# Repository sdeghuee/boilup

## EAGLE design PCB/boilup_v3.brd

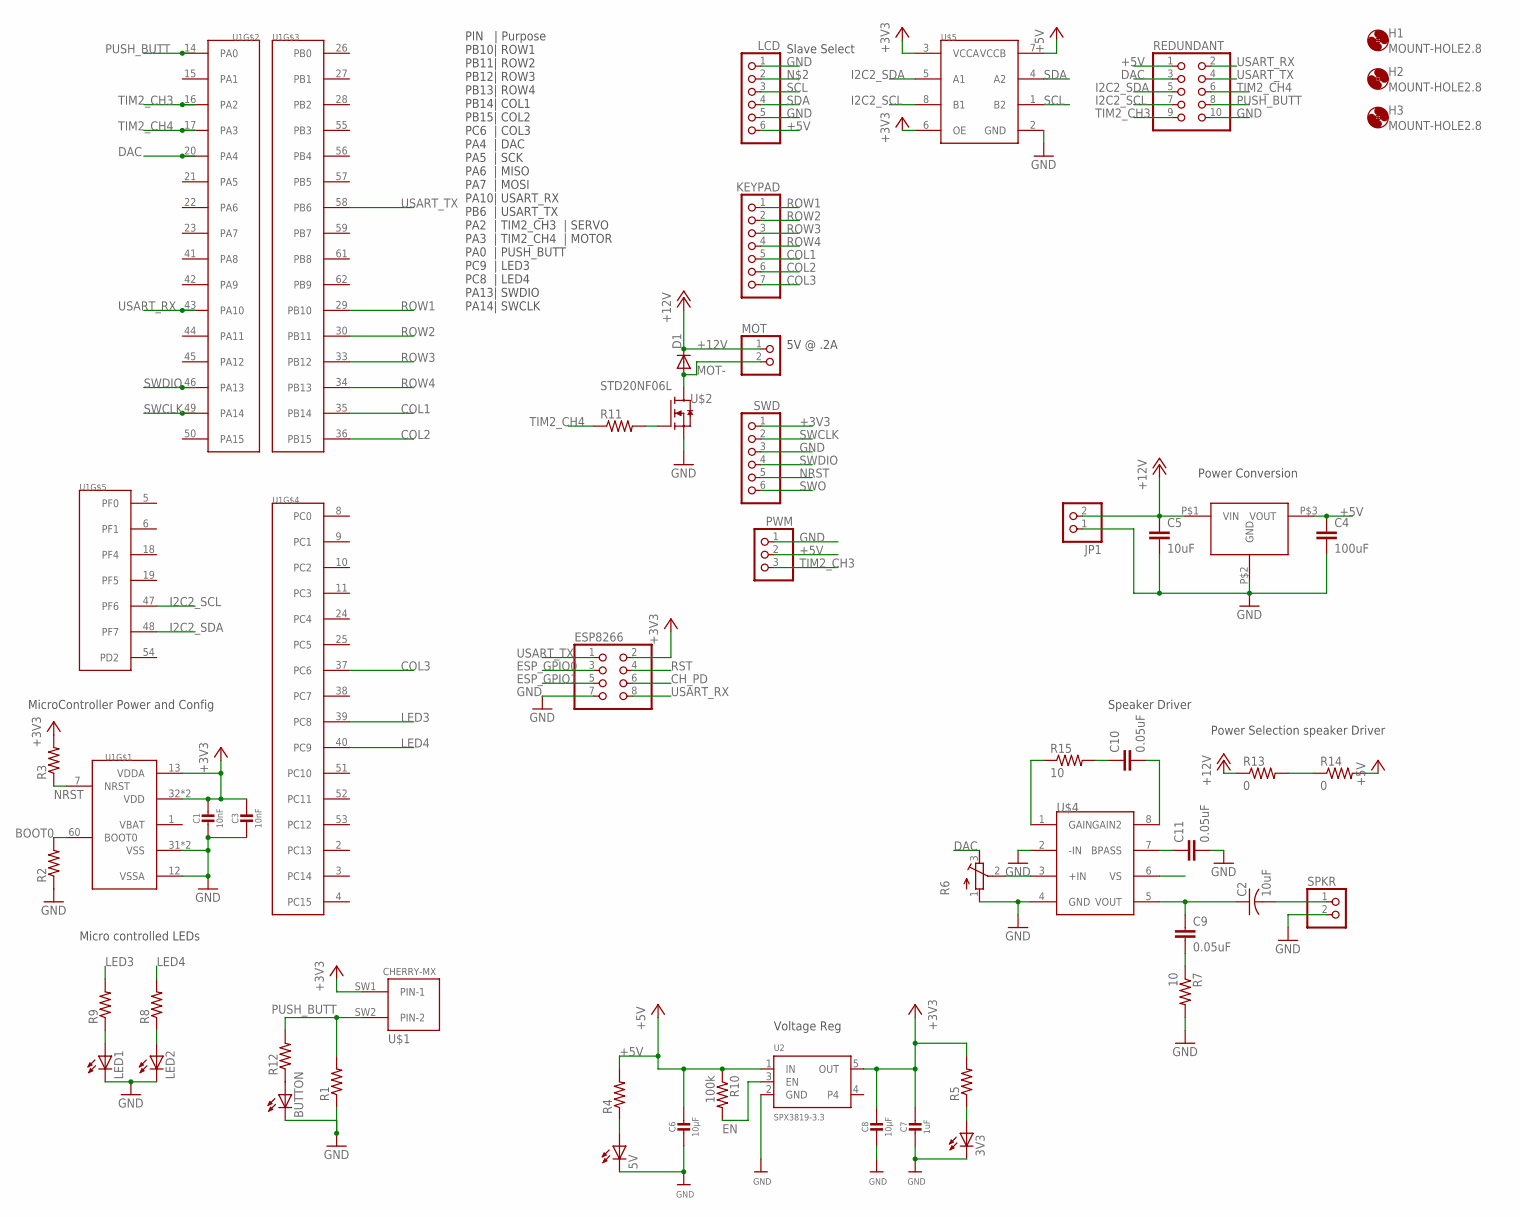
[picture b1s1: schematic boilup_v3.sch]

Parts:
3V3, 5V: LEDSML0805; SML0805
BUTTON: LEDSML0805; SML0805
C1, C3: 10nF; 0805-NO
C2: 10uF; C1210K
C4: 100uF; C1210K
C5: 10uF; C0603K
C6, C8: 10µF; 0805-NO
C7: 1uF; 0603-NO
C9, C10, C11: 0.05uF; C0603K
D1: DIODE-DO-214AC; DO-214AC
ESP8266: PINHD-2X4; 2X04
H1, H2, H3: MOUNT-HOLE2.8; 2,8
JP1: PINHD-1X2; 1X02
KEYPAD: PINHD-1X7; 1X07
LCD: PINHD-1X6; 1X06
LED1, LED2: LEDSML0805; SML0805
MOT: PINHD-1X2; 1X02
PWM: PINHD-1X3; 1X03
R1, R2, R3, R4, R5, R8, R9, R11, R12: R-US_R0603; R0603
R6: R-TRIMM3224X; RTRIM3224X
R7, R15: 10; R0603
R10: 100k; R0603
R13, R14: 0; R0603
REDUNDANT: PINHD-2X5; 2X05
SPKR: PINHD-1X2; 1X02
SWD: PINHD-1X6; 1X06
U1: STM32F0_LQFP64; QFP50P1200X1200X160-64N
U2: SPX3819-3.3; SOT23-5
U$1: CHERRY-MX
U$2: STD20NF06L; DPAK
U$3: TPSM842; TO-220
U$4: LM386; S-PDSO-G08
U$5: TXS0102; SOP-08

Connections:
+3V3: C1.1, C3.1, C7.1, C8.1, ESP8266.2, R3.2, R5.2, SWD.1, U1.13 (VDDA), U1.32 (VDD), U1.64 (VDD), U2.5 (OUT), U$1.SW1 (PIN-1), U$5.3 (VCCA), U$5.6 (OE); also elsewhere on the board
+5V: C4.1, C6.1, LCD.6, PWM.2, R4.2, R10.1, R14.2, REDUNDANT.1, U2.1 (IN), U$3.P$3 (VOUT), U$5.7 (VCCB); also elsewhere on the board
+12V: C5.1, D1.C, JP1.2, MOT.1, R13.1, U$3.P$1 (VIN); also elsewhere on the board
BOOT0: R2.2, U1.60 (BOOT0)
CH_PD: ESP8266.6
COL1: KEYPAD.5, U1.35 (PB14)
COL2: KEYPAD.6, U1.36 (PB15)
COL3: KEYPAD.7, U1.37 (PC6)
DAC: R6.3 (E), REDUNDANT.3, U1.20 (PA4)
EN: R10.2, U2.3 (EN)
ESP_GPIO0: ESP8266.3
ESP_GPIO1: ESP8266.5
GND: 3V3.C, 5V.C, BUTTON.C, C1.2, C3.2, C4.2, C5.2, C6.2, C7.2, C8.2, C11.2, ESP8266.7, JP1.1, LCD.1, LCD.5, LED1.C, LED2.C, PWM.1, R1.1, R2.1, R6.1 (A), R7.2, REDUNDANT.10, SPKR.2, SWD.3, U1.12 (VSSA), U1.31 (VSS), U1.63 (VSS), U2.2 (GND), U$2.P$2 (S), U$3.P$2 (GND), U$4.2 (-IN), U$4.4 (GND), U$5.2 (GND); also elsewhere on the board
I2C2_SCL: REDUNDANT.7, U1.47 (PF6), U$5.8 (B1); also elsewhere on the board
I2C2_SDA: REDUNDANT.5, U1.48 (PF7), U$5.5 (A1); also elsewhere on the board
LED3: R9.2, U1.39 (PC8)
LED4: R8.2, U1.40 (PC9)
MOT-: D1.A, MOT.2, U$2.P$1 (D); also elsewhere on the board
unnamed: LED2.A, R8.1
unnamed: LED1.A, R9.1
unnamed 21: R11.2, U$2.P$3 (G); also elsewhere on the board
unnamed: BUTTON.A, R12.1
unnamed: C9.2, R7.1
unnamed: 5V.A, R4.1
unnamed 25: C2.1, C9.1, U$4.5 (VOUT); also elsewhere on the board
unnamed 26: R6.2 (S), U$4.3 (+IN); also elsewhere on the board
unnamed 27: R15.1, U$4.1 (GAIN); also elsewhere on the board
unnamed 28: C10.2, U$4.8 (GAIN2); also elsewhere on the board
unnamed: C10.1, R15.2
unnamed 30: C11.1, U$4.7 (BPASS); also elsewhere on the board
unnamed: 3V3.A, R5.1
unnamed: C2.2, SPKR.1
NRST: R3.1, SWD.5, U1.7 (NRST)
OPAMPSUPPLY: R13.2, R14.1, U$4.6 (VS); also elsewhere on the board
PUSH_BUTT: R1.2, R12.2, REDUNDANT.8, U1.14 (PA0), U$1.SW2 (PIN-2)
ROW1: KEYPAD.1, U1.29 (PB10)
ROW2: KEYPAD.2, U1.30 (PB11)
ROW3: KEYPAD.3, U1.33 (PB12)
ROW4: KEYPAD.4, U1.34 (PB13)
RST: ESP8266.4
SCL: LCD.3, U$5.1 (B2); also elsewhere on the board
SDA: LCD.4, U$5.4 (A2); also elsewhere on the board
SWCLK: SWD.2, U1.49 (PA14)
SWDIO: SWD.4, U1.46 (PA13)
SWO: SWD.6
TIM2_CH3: PWM.3, REDUNDANT.9, U1.16 (PA2)
TIM2_CH4: R11.1, REDUNDANT.6, U1.17 (PA3)
USART_RX: ESP8266.8, REDUNDANT.2, U1.43 (PA10)
USART_TX: ESP8266.1, REDUNDANT.4, U1.58 (PB6)

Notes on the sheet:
PIN | Purpose PB10| ROW1 PB11| ROW2 PB12| ROW3 PB13| ROW4 PB14| COL1 PB15| COL2 PC6 | COL3 PA4 | DAC PA5 | SCK PA6 | MISO PA7 | MOSI PA10| USART_RX PB6 | USART_TX PA2 | TIM2_CH3 | SERVO PA3 | TIM2_CH4 | MOTOR PA0 | PUSH_BUTT PC9 | LED3 PC8 | LED4 PA13| SWDIO PA14| SWCLK
5V @ .2A
Voltage Reg
MicroController Power and Config
Power Conversion
Speaker Driver
Micro controlled LEDs
Power Selection speaker Driver
Slave Select

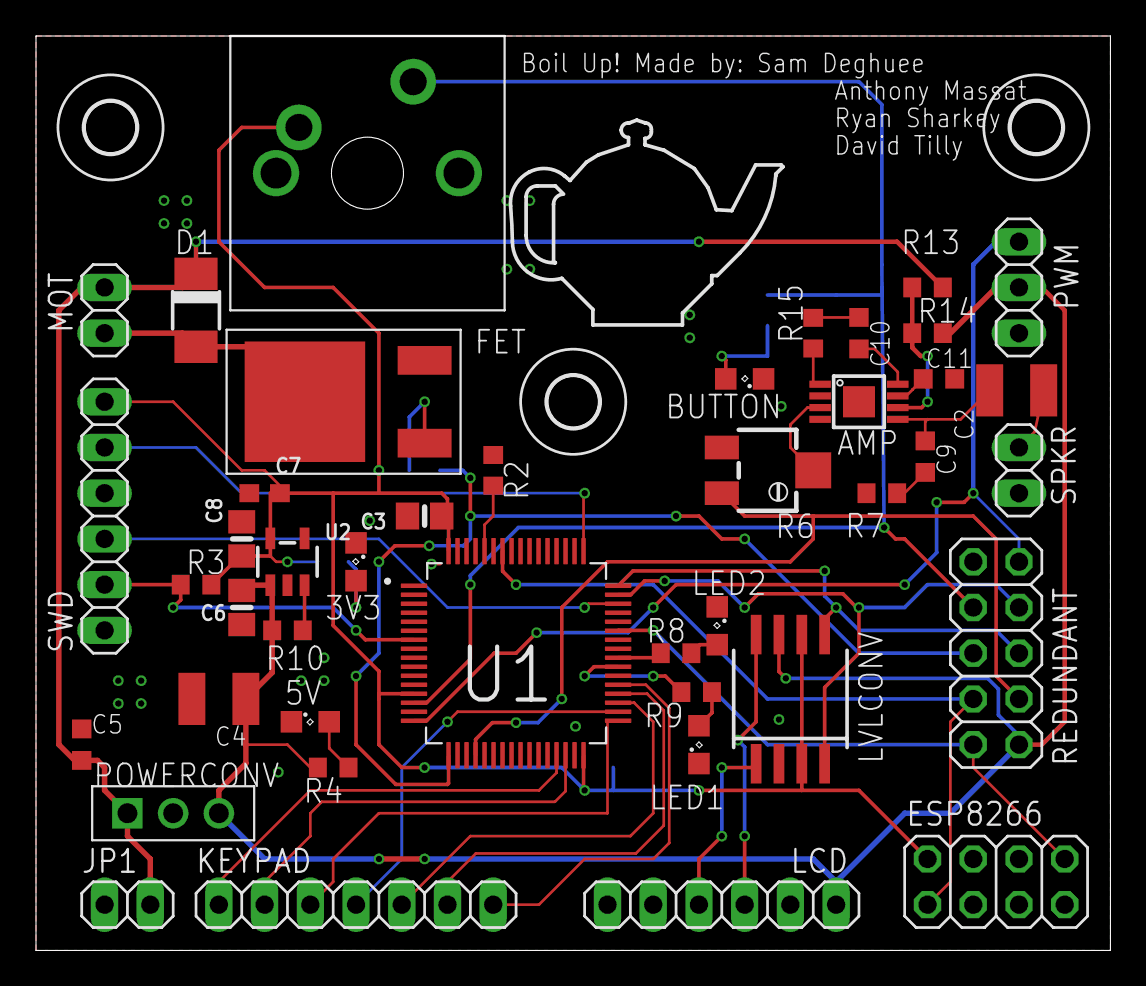
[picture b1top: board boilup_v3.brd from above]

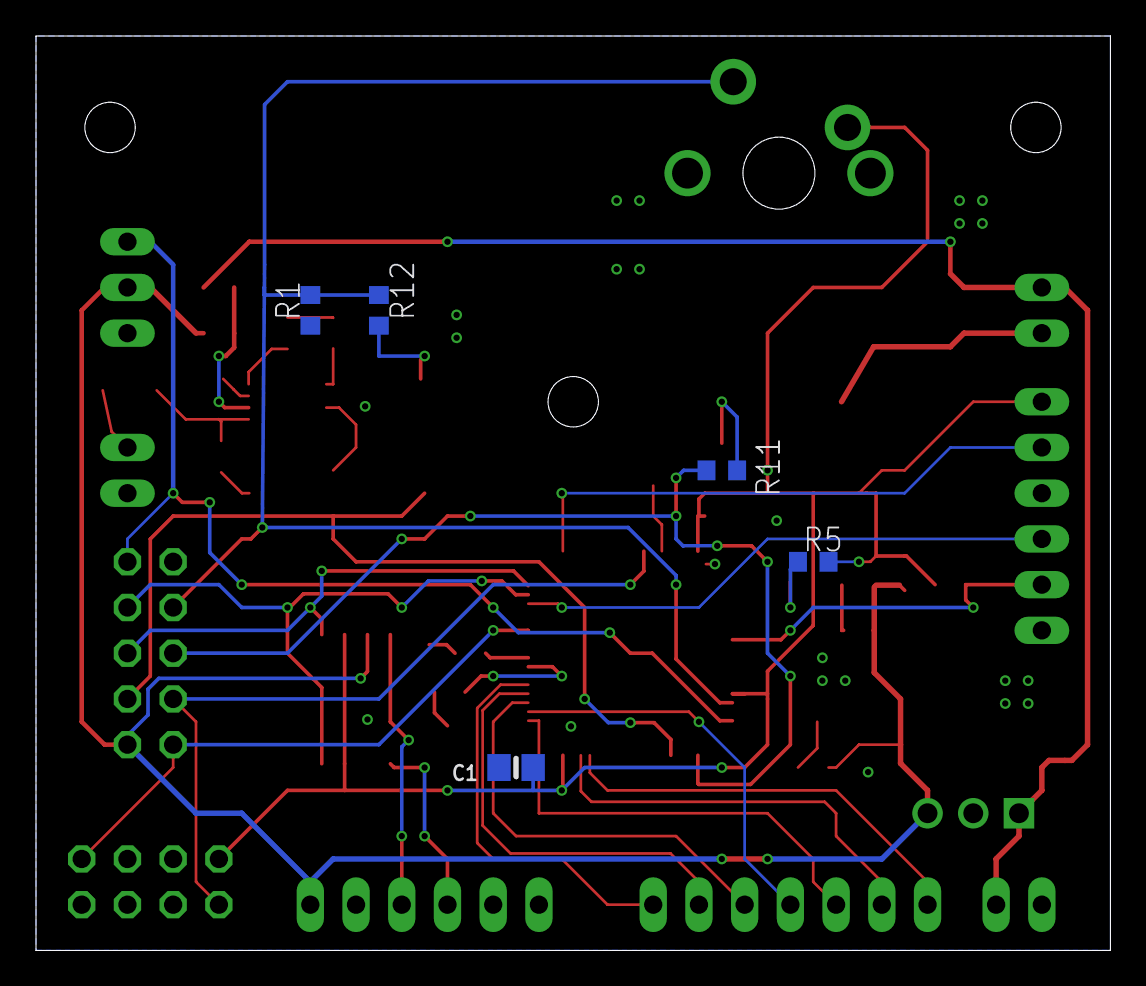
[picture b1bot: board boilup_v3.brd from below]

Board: 2 copper layers, 59.7 x 50.8 mm, 51 parts (5 on the bottom side), 44 nets.

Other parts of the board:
AMP: LM386; S-PDSO-G08
FET: STD20NF06L; DPAK
LVLCONV: TXS0102; SOP-08
POWERCONV: TPSM842; TO-220

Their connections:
+3V3: LVLCONV.3, LVLCONV.6; also elsewhere on the board
+5V: LVLCONV.7, POWERCONV.P$3; also elsewhere on the board
+12V: POWERCONV.P$1; also elsewhere on the board
GND: AMP.2, AMP.4, FET.P$2, LVLCONV.2, POWERCONV.P$2; also elsewhere on the board
I2C2_SCL: LVLCONV.4; also elsewhere on the board
I2C2_SDA: LVLCONV.5; also elsewhere on the board
MOT-: FET.P$1; also elsewhere on the board
unnamed 21: FET.P$3; also elsewhere on the board
unnamed 25: AMP.5; also elsewhere on the board
unnamed 26: AMP.3; also elsewhere on the board
unnamed 27: AMP.1; also elsewhere on the board
unnamed 28: AMP.8; also elsewhere on the board
unnamed 30: AMP.7; also elsewhere on the board
OPAMPSUPPLY: AMP.6; also elsewhere on the board
SCL: LVLCONV.1; also elsewhere on the board
SDA: LVLCONV.8; also elsewhere on the board

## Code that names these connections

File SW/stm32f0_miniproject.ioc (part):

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Mcu.Name=STM32F051R8Tx
Mcu.Package=LQFP64
Mcu.UserName=STM32F051R8Tx
PA0.GPIOParameters=GPIO_Label,GPIO_ModeDefaultEXTI
PA0.GPIO_Label=B1 [Blue PushButton]
PA0.GPIO_ModeDefaultEXTI=GPIO_MODE_EVT_RISING
PA0.Signal=GPXTI0
PA10.Mode=Asynchronous
PA10.Signal=USART1_RX
PA13.GPIOParameters=GPIO_Label
PA13.GPIO_Label=SWDIO
PA13.Signal=SYS_SWDIO
PA14.GPIOParameters=GPIO_Label
PA14.GPIO_Label=SWCLK
PA14.Signal=SYS_SWCLK
PA2.Signal=S_TIM2_CH3
PA3.Signal=S_TIM2_CH4
PA4.Signal=COMP_DAC11_group
PB10.Signal=GPIO_Input
PB11.Signal=GPIO_Input
PB12.Signal=GPIO_Input
PB13.Signal=GPIO_Input
PB14.Signal=GPIO_Output
PB15.Signal=GPIO_Output
PB6.Mode=Asynchronous
PB6.Signal=USART1_TX
PC6.Signal=GPIO_Output
PC8.GPIOParameters=GPIO_Label
PC8.GPIO_Label=LD4 [Blue Led]
PC8.Signal=GPIO_Output
PC9.GPIOParameters=GPIO_Label
PC9.GPIO_Label=LD3 [Green Led]
PC9.Signal=GPIO_Output
PF6.Mode=I2C
PF6.Signal=I2C2_SCL
PF7.Mode=I2C
PF7.Signal=I2C2_SDA
RCC.SYSCLKFreq_VALUE=48000000
RCC.SYSCLKSource=RCC_SYSCLKSOURCE_PLLCLK
board=STM32F0DISCOVERY
boardIOC=true

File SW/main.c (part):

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  /* USER CODE END WHILE */

  /* USER CODE BEGIN 3 */
//      HAL_GPIO_WritePin(COL2_PORT, COL2_PIN, 1);
//      HAL_GPIO_WritePin(COL3_PORT, COL3_PIN, 1);
//      HAL_GPIO_WritePin(COL1_PORT, COL1_PIN, 0);
//      int tmp = ROW1_PIN;
//      if (HAL_GPIO_ReadPin(ROW1_PORT, ROW1_PIN) & tmp) {
//          HAL_GPIO_WritePin(LD3_GPIO_Port, LD3_Pin, 1);
//      }
//      else {
//          HAL_GPIO_WritePin(LD3_GPIO_Port, LD3_Pin, 0);
//      }
//      HAL_GPIO_WritePin(COL1_PORT, COL1_PIN, 1);
      if (buttonPress) {
          buttonPress = 0;
          HAL_GPIO_TogglePin(LD4_GPIO_Port, LD4_Pin);
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  GPIO_InitStruct.Pull = GPIO_NOPULL;
  HAL_GPIO_Init(B1_GPIO_Port, &GPIO_InitStruct);

  /*Configure GPIO pins : PB10 PB11 PB12 PB13 */
  GPIO_InitStruct.Pin = GPIO_PIN_10|GPIO_PIN_11|GPIO_PIN_12|GPIO_PIN_13;
  GPIO_InitStruct.Mode = GPIO_MODE_INPUT;
  GPIO_InitStruct.Pull = GPIO_NOPULL;
  HAL_GPIO_Init(GPIOB, &GPIO_InitStruct);

  /*Configure GPIO pins : PB14 PB15 */
  GPIO_InitStruct.Pin = GPIO_PIN_14|GPIO_PIN_15;
  GPIO_InitStruct.Mode = GPIO_MODE_OUTPUT_PP;
  GPIO_InitStruct.Pull = GPIO_NOPULL;
  GPIO_InitStruct.Speed = GPIO_SPEED_FREQ_LOW;
  HAL_GPIO_Init(GPIOB, &GPIO_InitStruct);

  /*Configure GPIO pins : PC6 LD4_Pin LD3_Pin */
  GPIO_InitStruct.Pin = GPIO_PIN_6|LD4_Pin|LD3_Pin;
  GPIO_InitStruct.Mode = GPIO_MODE_OUTPUT_PP;
  GPIO_InitStruct.Pull = GPIO_NOPULL;
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
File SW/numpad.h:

/*
 * numpad.h
 *
 *  Created on: Apr 17, 2018
 *      Author: david
 */

#ifndef NUMPAD_H_
#define NUMPAD_H_

#define ROW1_PORT	GPIOB
#define ROW2_PORT	GPIOB
#define ROW3_PORT	GPIOB
#define ROW4_PORT	GPIOB
#define COL1_PORT	GPIOB
#define COL2_PORT	GPIOB
#define COL3_PORT	GPIOC
#define ROW1_PIN	GPIO_PIN_10
#define ROW2_PIN	GPIO_PIN_11
#define ROW3_PIN	GPIO_PIN_12
#define ROW4_PIN	GPIO_PIN_13
#define COL1_PIN	GPIO_PIN_14
#define COL2_PIN	GPIO_PIN_15
#define COL3_PIN	GPIO_PIN_6

void matrixDebounce(uint32_t column);
uint32_t matrixButtonDebounce(uint32_t index);

void matrixDebounce(uint32_t column){
    switch (column) {
        case 1:
//            GPIOC->ODR |= 0x00001000;//col3
//            GPIOD->ODR |= 0x00000004;//col2
//            GPIOB->ODR &= 0xFFFFFFF7;//col1
            HAL_GPIO_WritePin(COL2_PORT, COL2_PIN, 1);
            HAL_GPIO_WritePin(COL3_PORT, COL3_PIN, 1);
            HAL_GPIO_WritePin(COL1_PORT, COL1_PIN, 0);
            break;
        case 2:
//            GPIOB->ODR |= 0x00000008;
//            GPIOC->ODR |= 0x00001000;
//            GPIOD->ODR &= 0xFFFFFFFB;
            HAL_GPIO_WritePin(COL1_PORT, COL1_PIN, 1);
            HAL_GPIO_WritePin(COL3_PORT, COL3_PIN, 1);
            HAL_GPIO_WritePin(COL2_PORT, COL2_PIN, 0);
            break;
        case 3:
//            GPIOB->ODR |= 0x00000008;
//            GPIOD->ODR |= 0x00000004;
//            GPIOC->ODR &= 0xFFFFEFFF;
            HAL_GPIO_WritePin(COL1_PORT, COL1_PIN, 1);
            HAL_GPIO_WritePin(COL2_PORT, COL2_PIN, 1);
            HAL_GPIO_WritePin(COL3_PORT, COL3_PIN, 0);
            break;
    }
    for (uint32_t row = 0; row < 4; row++) {
//        btnCurrent[(column - 1)*4 + row] = !(GPIOB->IDR & (0x10 << (3-row)));
        switch (row) {
            case 0:
                btnCurrent[(column - 1)*4 + row] = !(HAL_GPIO_ReadPin(GPIOB, GPIO_PIN_10));
                break;
            case 1:
                btnCurrent[(column - 1)*4 + row] = !(HAL_GPIO_ReadPin(GPIOB, GPIO_PIN_11));
                break;
            case 2:
                btnCurrent[(column - 1)*4 + row] = !(HAL_GPIO_ReadPin(GPIOB, GPIO_PIN_12));
                break;
            case 3:
                btnCurrent[(column - 1)*4 + row] = !(HAL_GPIO_ReadPin(GPIOB, GPIO_PIN_13));
                break;
        }
//        uint32_t a = !(GPIOB->IDR & (0x400 << row));
//        btnCurrent[(column - 1)*4 + row] = a;
        matrixButtonDebounce((column - 1)*4 + row);
    }
}

uint32_t matrixButtonDebounce(uint32_t index) {
    btnPress[index] = !btnPrevious[index] && btnCurrent[index];
    btnPrevious[index] = btnCurrent[index];
}

#endif /* NUMPAD_H_ */

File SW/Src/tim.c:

/**
  ******************************************************************************
  * File Name          : TIM.c
  * Description        : This file provides code for the configuration
  *                      of the TIM instances.
  ******************************************************************************
  ** This notice applies to any and all portions of this file
  * that are not between comment pairs USER CODE BEGIN and
  * USER CODE END. Other portions of this file, whether 
  * inserted by the user or by software development tools
  * are owned by their respective copyright owners.
  *
  * COPYRIGHT(c) 2018 STMicroelectronics
  *
  * Redistribution and use in source and binary forms, with or without modification,
  * are permitted provided that the following conditions are met:
  *   1. Redistributions of source code must retain the above copyright notice,
  *      this list of conditions and the following disclaimer.
  *   2. Redistributions in binary form must reproduce the above copyright notice,
  *      this list of conditions and the following disclaimer in the documentation
  *      and/or other materials provided with the distribution.
  *   3. Neither the name of STMicroelectronics nor the names of its contributors
  *      may be used to endorse or promote products derived from this software
  *      without specific prior written permission.
  *
  * THIS SOFTWARE IS PROVIDED BY THE COPYRIGHT HOLDERS AND CONTRIBUTORS "AS IS"
  * AND ANY EXPRESS OR IMPLIED WARRANTIES, INCLUDING, BUT NOT LIMITED TO, THE
  * IMPLIED WARRANTIES OF MERCHANTABILITY AND FITNESS FOR A PARTICULAR PURPOSE ARE
  * DISCLAIMED. IN NO EVENT SHALL THE COPYRIGHT HOLDER OR CONTRIBUTORS BE LIABLE
  * FOR ANY DIRECT, INDIRECT, INCIDENTAL, SPECIAL, EXEMPLARY, OR CONSEQUENTIAL
  * DAMAGES (INCLUDING, BUT NOT LIMITED TO, PROCUREMENT OF SUBSTITUTE GOODS OR
  * SERVICES; LOSS OF USE, DATA, OR PROFITS; OR BUSINESS INTERRUPTION) HOWEVER
  * CAUSED AND ON ANY THEORY OF LIABILITY, WHETHER IN CONTRACT, STRICT LIABILITY,
  * OR TORT (INCLUDING NEGLIGENCE OR OTHERWISE) ARISING IN ANY WAY OUT OF THE USE
  * OF THIS SOFTWARE, EVEN IF ADVISED OF THE POSSIBILITY OF SUCH DAMAGE.
  *
  ******************************************************************************
  */

/* Includes ------------------------------------------------------------------*/
#include "tim.h"

/* USER CODE BEGIN 0 */
uint8_t updatePump = 0;
/* USER CODE END 0 */

TIM_HandleTypeDef htim2;
TIM_HandleTypeDef htim3;
TIM_HandleTypeDef htim14;

/* TIM2 init function */
void MX_TIM2_Init(void)
{
  TIM_ClockConfigTypeDef sClockSourceConfig;
  TIM_MasterConfigTypeDef sMasterConfig;
  TIM_OC_InitTypeDef sConfigOC;

  htim2.Instance = TIM2;
  htim2.Init.Prescaler = 937;
  htim2.Init.CounterMode = TIM_COUNTERMODE_UP;
  htim2.Init.Period = 1024;
  htim2.Init.ClockDivision = TIM_CLOCKDIVISION_DIV1;
  htim2.Init.AutoReloadPreload = TIM_AUTORELOAD_PRELOAD_DISABLE;
  if (HAL_TIM_Base_Init(&htim2) != HAL_OK)
  {
    _Error_Handler(__FILE__, __LINE__);
  }

  sClockSourceConfig.ClockSource = TIM_CLOCKSOURCE_INTERNAL;
  if (HAL_TIM_ConfigClockSource(&htim2, &sClockSourceConfig) != HAL_OK)
  {
    _Error_Handler(__FILE__, __LINE__);
  }

  if (HAL_TIM_PWM_Init(&htim2) != HAL_OK)
  {
    _Error_Handler(__FILE__, __LINE__);
  }

  sMasterConfig.MasterOutputTrigger = TIM_TRGO_RESET;
  sMasterConfig.MasterSlaveMode = TIM_MASTERSLAVEMODE_DISABLE;
  if (HAL_TIMEx_MasterConfigSynchronization(&htim2, &sMasterConfig) != HAL_OK)
  {
    _Error_Handler(__FILE__, __LINE__);
  }

  sConfigOC.OCMode = TIM_OCMODE_PWM1;
  sConfigOC.Pulse = 0;
  sConfigOC.OCPolarity = TIM_OCPOLARITY_HIGH;
  sConfigOC.OCFastMode = TIM_OCFAST_DISABLE;
  if (HAL_TIM_PWM_ConfigChannel(&htim2, &sConfigOC, TIM_CHANNEL_3) != HAL_OK)
  {
    _Error_Handler(__FILE__, __LINE__);
  }

  if (HAL_TIM_PWM_ConfigChannel(&htim2, &sConfigOC, TIM_CHANNEL_4) != HAL_OK)
  {
    _Error_Handler(__FILE__, __LINE__);
  }

  HAL_TIM_MspPostInit(&htim2);

}
/* TIM3 init function */
void MX_TIM3_Init(void)
{
  TIM_ClockConfigTypeDef sClockSourceConfig;
  TIM_MasterConfigTypeDef sMasterConfig;

  htim3.Instance = TIM3;
  htim3.Init.Prescaler = 47;
  htim3.Init.CounterMode = TIM_COUNTERMODE_UP;
  htim3.Init.Period = 999;
  htim3.Init.ClockDivision = TIM_CLOCKDIVISION_DIV1;
  htim3.Init.AutoReloadPreload = TIM_AUTORELOAD_PRELOAD_DISABLE;
  if (HAL_TIM_Base_Init(&htim3) != HAL_OK)
  {
    _Error_Handler(__FILE__, __LINE__);
  }

  sClockSourceConfig.ClockSource = TIM_CLOCKSOURCE_INTERNAL;
  if (HAL_TIM_ConfigClockSource(&htim3, &sClockSourceConfig) != HAL_OK)
  {
    _Error_Handler(__FILE__, __LINE__);
  }

  sMasterConfig.MasterOutputTrigger = TIM_TRGO_RESET;
  sMasterConfig.MasterSlaveMode = TIM_MASTERSLAVEMODE_DISABLE;
  if (HAL_TIMEx_MasterConfigSynchronization(&htim3, &sMasterConfig) != HAL_OK)
  {
    _Error_Handler(__FILE__, __LINE__);
  }

}
/* TIM14 init function */
void MX_TIM14_Init(void)
{

  htim14.Instance = TIM14;
  htim14.Init.Prescaler = 399;
  htim14.Init.CounterMode = TIM_COUNTERMODE_UP;
  htim14.Init.Period = 1;
  htim14.Init.ClockDivision = TIM_CLOCKDIVISION_DIV1;
  htim14.Init.AutoReloadPreload = TIM_AUTORELOAD_PRELOAD_DISABLE;
  if (HAL_TIM_Base_Init(&htim14) != HAL_OK)
  {
    _Error_Handler(__FILE__, __LINE__);
  }

}

void HAL_TIM_Base_MspInit(TIM_HandleTypeDef* tim_baseHandle)
{

  if(tim_baseHandle->Instance==TIM2)
  {
  /* USER CODE BEGIN TIM2_MspInit 0 */

  /* USER CODE END TIM2_MspInit 0 */
    /* TIM2 clock enable */
    __HAL_RCC_TIM2_CLK_ENABLE();

    /* TIM2 interrupt Init */
    HAL_NVIC_SetPriority(TIM2_IRQn, 0, 0);
    HAL_NVIC_EnableIRQ(TIM2_IRQn);
  /* USER CODE BEGIN TIM2_MspInit 1 */

  /* USER CODE END TIM2_MspInit 1 */
  }
  else if(tim_baseHandle->Instance==TIM3)
  {
  /* USER CODE BEGIN TIM3_MspInit 0 */

  /* USER CODE END TIM3_MspInit 0 */
    /* TIM3 clock enable */
    __HAL_RCC_TIM3_CLK_ENABLE();

    /* TIM3 interrupt Init */
    HAL_NVIC_SetPriority(TIM3_IRQn, 0, 0);
    HAL_NVIC_EnableIRQ(TIM3_IRQn);
  /* USER CODE BEGIN TIM3_MspInit 1 */

  /* USER CODE END TIM3_MspInit 1 */
  }
  else if(tim_baseHandle->Instance==TIM14)
  {
  /* USER CODE BEGIN TIM14_MspInit 0 */

  /* USER CODE END TIM14_MspInit 0 */
    /* TIM14 clock enable */
    __HAL_RCC_TIM14_CLK_ENABLE();

    /* TIM14 interrupt Init */
    HAL_NVIC_SetPriority(TIM14_IRQn, 0, 0);
    HAL_NVIC_EnableIRQ(TIM14_IRQn);
  /* USER CODE BEGIN TIM14_MspInit 1 */

  /* USER CODE END TIM14_MspInit 1 */
  }
}
void HAL_TIM_MspPostInit(TIM_HandleTypeDef* timHandle)
{

  GPIO_InitTypeDef GPIO_InitStruct;
  if(timHandle->Instance==TIM2)
  {
  /* USER CODE BEGIN TIM2_MspPostInit 0 */

  /* USER CODE END TIM2_MspPostInit 0 */
  
    /**TIM2 GPIO Configuration    
    PA2     ------> TIM2_CH3
    PA3     ------> TIM2_CH4 
    */
    GPIO_InitStruct.Pin = GPIO_PIN_2|GPIO_PIN_3;
    GPIO_InitStruct.Mode = GPIO_MODE_AF_PP;
    GPIO_InitStruct.Pull = GPIO_NOPULL;
    GPIO_InitStruct.Speed = GPIO_SPEED_FREQ_LOW;
    GPIO_InitStruct.Alternate = GPIO_AF2_TIM2;
    HAL_GPIO_Init(GPIOA, &GPIO_InitStruct);

  /* USER CODE BEGIN TIM2_MspPostInit 1 */

  /* USER CODE END TIM2_MspPostInit 1 */
  }

}

void HAL_TIM_Base_MspDeInit(TIM_HandleTypeDef* tim_baseHandle)
{

  if(tim_baseHandle->Instance==TIM2)
  {
  /* USER CODE BEGIN TIM2_MspDeInit 0 */

  /* USER CODE END TIM2_MspDeInit 0 */
    /* Peripheral clock disable */
    __HAL_RCC_TIM2_CLK_DISABLE();

    /* TIM2 interrupt Deinit */
    HAL_NVIC_DisableIRQ(TIM2_IRQn);
  /* USER CODE BEGIN TIM2_MspDeInit 1 */

  /* USER CODE END TIM2_MspDeInit 1 */
  }
  else if(tim_baseHandle->Instance==TIM3)
  {
  /* USER CODE BEGIN TIM3_MspDeInit 0 */

  /* USER CODE END TIM3_MspDeInit 0 */
    /* Peripheral clock disable */
    __HAL_RCC_TIM3_CLK_DISABLE();

    /* TIM3 interrupt Deinit */
    HAL_NVIC_DisableIRQ(TIM3_IRQn);
  /* USER CODE BEGIN TIM3_MspDeInit 1 */

  /* USER CODE END TIM3_MspDeInit 1 */
  }
  else if(tim_baseHandle->Instance==TIM14)
  {
  /* USER CODE BEGIN TIM14_MspDeInit 0 */

  /* USER CODE END TIM14_MspDeInit 0 */
    /* Peripheral clock disable */
    __HAL_RCC_TIM14_CLK_DISABLE();

    /* TIM14 interrupt Deinit */
    HAL_NVIC_DisableIRQ(TIM14_IRQn);
  /* USER CODE BEGIN TIM14_MspDeInit 1 */

  /* USER CODE END TIM14_MspDeInit 1 */
  }
} 

/* USER CODE BEGIN 1 */
void servoDown(){
    // moves the servo down to flip the switch
	__HAL_TIM_SET_COMPARE(&htim2,TIM_CHANNEL_3,90);
}
void servoUp(){
    // moves the servo up to disengage the switch
	__HAL_TIM_SET_COMPARE(&htim2,TIM_CHANNEL_3,120);
}
/* USER CODE END 1 */

/**
  * @}
  */

/**
  * @}
  */

/************************ (C) COPYRIGHT STMicroelectronics *****END OF FILE****/

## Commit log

2018-03-26 Initial PCB and Schematic
2018-03-26 More updates
2018-03-27 Initial routing + pinout
2018-03-27 Mechanical export
2018-03-27 DXF created
2018-03-28 Updated CAD and PCB
2018-04-02 Added V2 brd layout
2018-04-05 replaced speaker circuit, redid board layout. V2 is active development version
2018-04-06 More small updates. check v2
2018-04-06 removed backup boards
2018-04-08 v3 using i2c and a level shifter
2018-04-08 sam is not a smart boy, fixed logic
2018-04-08 Final revisions and Kettle addition
2018-04-09 added mechancial updates
2018-04-09 Mechanical design with final PCB
    and better assembly management
2018-04-09 Fillets to make it printable
    110mm is a pain
2018-04-09 Further mechanical considerations
2018-04-10 Printing kettlefoot with larger latch
2018-04-10 Added SW files for testing I2C
    Includes library for display commands
2018-04-10 Rename displaycommands.h to SW/displaycommands.h
2018-04-10 Rename main.c to SW/main.c
2018-04-10 Rename stm32f0_i2c_display.ioc to SW/stm32f0_i2c_display.ioc
2018-04-11 Created non PCB variant of kettle foot
2018-04-11 didnt push the stl
2018-04-12 Added Servo Hook
2018-04-12 Edit NO PCB to be taller and larger hole
2018-04-12 servo hook v2
2018-04-13 Initial Print upsidedown switch
2018-04-13 upsidedown switch v2
2018-04-13 pushypushy
2018-04-15 More updates start of keycap design
2018-04-17 Adding core code configuration
2018-04-17 Added code for numpad
2018-04-18 reworked configuration to make separate files for each peripheral initialization and logic
2018-04-20 added temporary ESP functions before reworking
2018-04-21 implemented finish tea song
2018-04-21 updated dac and added state machine stages for songs
2018-04-21 combined everybody's code and added time functionality
2018-04-21 forgot to add some peripheral last commit
2018-04-22 fixed main.c
2018-04-22 added servo code
2018-04-22 fixed 24 hour clock
2018-04-22 added servo functions prototypes
2018-04-23 added state machine, along with struct for storing times
2018-04-23 finalized code for demonstration
2018-04-26 finalized code without slackbot integration; including reworked state machine, enums for states, quieter FF victory theme, more reliable display
2018-04-27 added slack integration (/teatime)
2018-04-27 fixed slack commands only setting alarms in the AM
2018-04-27 final presentation version
2018-04-29 added comments for files I worked on

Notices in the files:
parts and their libraries:
microbuilder: This work is placed in the public domain, and may be freely used for commercial and non-commercial work with the following conditions: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
